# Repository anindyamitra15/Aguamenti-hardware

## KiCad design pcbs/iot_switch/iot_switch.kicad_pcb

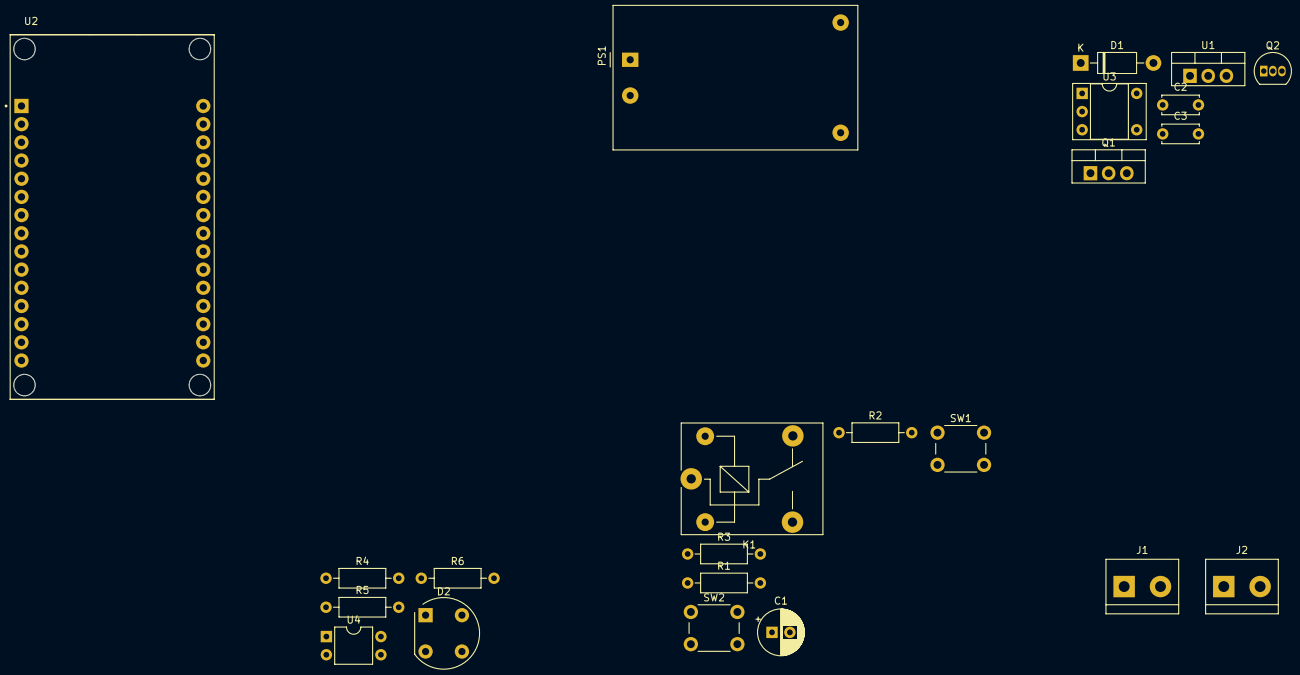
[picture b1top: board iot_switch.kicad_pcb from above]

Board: 2 copper layers, 23 parts (0 on the bottom side), 22 nets, no tracks yet.

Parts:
C1: 100uF; CP_Radial_D6.3mm_P2.50mm
C2, C3: 100nF; C_Disc_D5.0mm_W2.5mm_P5.00mm
D1: 1N4007; D_DO-41_SOD81_P10.16mm_Horizontal
D2: W10G; Diode_Bridge_Round_D9.8mm
J1: AC IN; TerminalBlock_bornier-2_P5.08mm
J2: LOAD OUT; TerminalBlock_bornier-2_P5.08mm
K1: SANYOU_SRD_Form_C; Relay_SPDT_SANYOU_SRD_Series_Form_C
PS1: HLK-PM12; Converter_ACDC_HiLink_HLK-PMxx
Q1: BT136-500; TO-220-3_Vertical
Q2: BC547; TO-92_Inline
R1, R3: 1k; R_Axial_DIN0207_L6.3mm_D2.5mm_P10.16mm_Horizontal
R2: 330; R_Axial_DIN0207_L6.3mm_D2.5mm_P10.16mm_Horizontal
R4, R5: 100k; R_Axial_DIN0207_L6.3mm_D2.5mm_P10.16mm_Horizontal
R6: 10k; R_Axial_DIN0207_L6.3mm_D2.5mm_P10.16mm_Horizontal
SW1: L1 Switch; SW_PUSH_6mm
SW2: L2 Switch; SW_PUSH_6mm
U1: L7805; TO-220-3_Vertical
U2: ESP32-DEVKIT-V1; MODULE_ESP32_DEVKIT_V1
U3: MOC3021M; DIP-5-6_W7.62mm_Socket
U4: PC817; DIP-4_W7.62mm

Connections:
+3V3: R6.1, U2.1
+5V: C3.1, U1.3, U2.30
+12V: C1.1, C2.1, D1.1, K1.2, PS1.4, U1.1
GND: C1.2, C2.2, C3.2, PS1.3, Q2.3, SW1.2, SW2.2, U1.2, U2.2, U2.29, U3.2, U4.3
L1: R1.2, U2.14
L2: R3.2, U2.15
Live: J1.1, K1.1, PS1.1, Q1.2, R4.1, U3.6
unnamed: D1.2, K1.5, Q2.1
unnamed: D2.1, U4.1
unnamed: D2.2, R5.2
unnamed: D2.3, U4.2
unnamed: J2.1, Q1.1
unnamed: J2.2, K1.3
unnamed: Q1.3, R2.1
unnamed: Q2.2, R3.1
unnamed: R1.1, U3.1
unnamed: R2.2, U3.4
unnamed: R4.2, R5.1
unnamed: SW1.1, U2.24
unnamed: SW2.1, U2.25
Neutral: D2.4, J1.2, PS1.2
ZVD: R6.2, U2.9, U4.4

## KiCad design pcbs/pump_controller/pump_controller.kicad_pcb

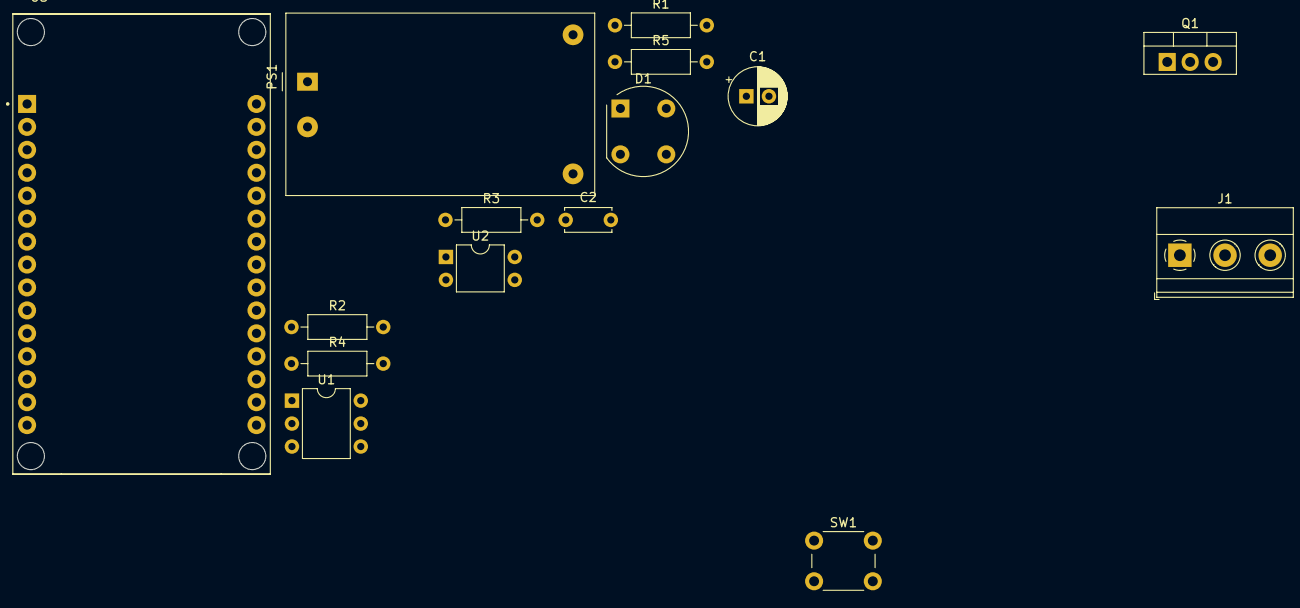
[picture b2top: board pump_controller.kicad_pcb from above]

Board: 2 copper layers, 15 parts (0 on the bottom side), 16 nets, no tracks yet.

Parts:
C1: 100uF; CP_Radial_D6.3mm_P2.50mm
C2: 100nF; C_Disc_D5.0mm_W2.5mm_P5.00mm
D1: W10G; Diode_Bridge_Round_D9.8mm
J1: AC_CON; TerminalBlock_Phoenix_MKDS-1,5-3_1x03_P5.00mm_Horizontal
PS1: HLK-PM01; Converter_ACDC_HiLink_HLK-PMxx
Q1: BTA16-800BW; TO-220-3_Vertical
R1, R2: 100k; R_Axial_DIN0207_L6.3mm_D2.5mm_P10.16mm_Horizontal
R3: 470; R_Axial_DIN0207_L6.3mm_D2.5mm_P10.16mm_Horizontal
R4: 1k; R_Axial_DIN0207_L6.3mm_D2.5mm_P10.16mm_Horizontal
R5: 10k; R_Axial_DIN0207_L6.3mm_D2.5mm_P10.16mm_Horizontal
SW1: Control Switch; SW_PUSH_6mm
U1: MOC3021M; DIP-6_W7.62mm
U2: PC817; DIP-4_W7.62mm
U3: ESP32-DEVKIT-V1; MODULE_ESP32_DEVKIT_V1

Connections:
+3V3: R5.1, U3.1
+5V: C1.1, C2.1, PS1.4, U3.30
Drive: R4.2, U3.6
GND: C1.2, C2.2, PS1.3, SW1.2, U1.2, U2.3, U3.2, U3.29
unnamed: D1.1, U2.1
unnamed: D1.2, R2.2
unnamed: D1.3, U2.2
unnamed: D1.4, J1.2, PS1.1, Q1.2, U1.4
unnamed: J1.1, Q1.1
unnamed: J1.3, PS1.2, R1.1
unnamed: Q1.3, R3.1
unnamed: R1.2, R2.1
unnamed: R3.2, U1.6
unnamed: R4.1, U1.1
unnamed: SW1.1, U3.7
ZVD: R5.2, U2.4, U3.9

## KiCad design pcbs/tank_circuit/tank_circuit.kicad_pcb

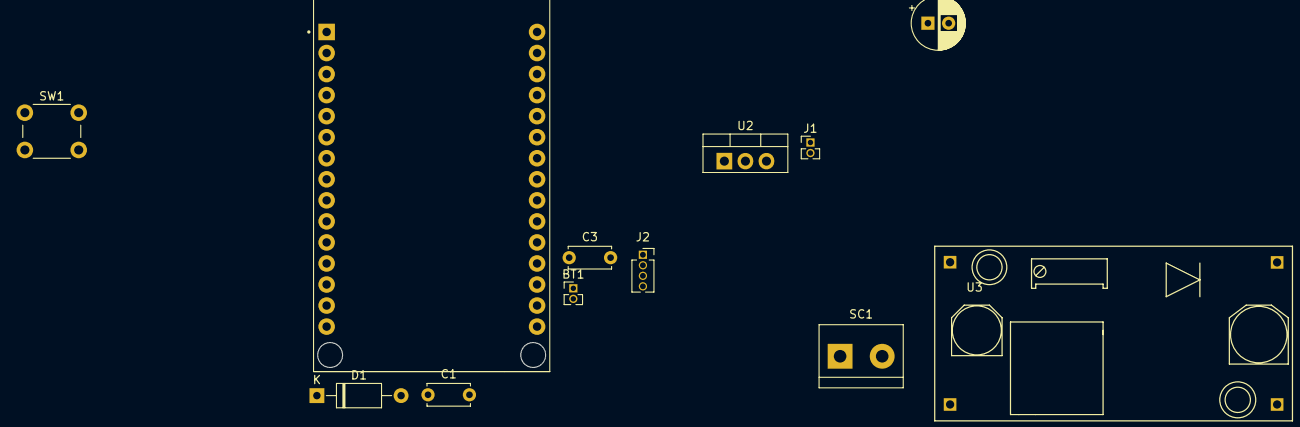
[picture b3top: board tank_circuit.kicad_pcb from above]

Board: 2 copper layers, 12 parts (0 on the bottom side), 10 nets, no tracks yet.

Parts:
BT1: 7.4V Li-ion; PinHeader_1x02_P1.27mm_Vertical
C1, C3: 100nF; C_Disc_D5.0mm_W2.5mm_P5.00mm
C2: 100uF; CP_Radial_D6.3mm_P2.50mm
D1: D_Schottky; D_A-405_P10.16mm_Horizontal
J1: Overflow detect; PinHeader_1x02_P1.27mm_Vertical
J2: Ultrasonic sensor; PinSocket_1x04_P1.27mm_Vertical
SC1: Solar_Cells; TerminalBlock_bornier-2_P5.08mm
SW1: Calibration mode; SW_PUSH_6mm
U1: ESP32-DEVKIT-V1; MODULE_ESP32_DEVKIT_V1
U2: LM7805_TO220; TO-220-3_Vertical
U3: XL6009; XL6009_module

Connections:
+5V: C1.1, J2.1, U1.30, U2.3
+VDC: BT1.1, C2.1, C3.1, D1.1, U2.1
GND: BT1.2, C1.2, C2.2, C3.2, J1.2, J2.4, SW1.2, U1.2, U1.29, U2.2, U3.3
unnamed: D1.2, U3.4
unnamed: J1.1, U1.9
unnamed: J2.2, U1.6
unnamed: J2.3, U1.7
unnamed: SC1.1, U3.1
unnamed: SC1.2, U3.2
unnamed: SW1.1, U1.10

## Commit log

2022-10-16 init
2022-10-16 some info
2022-10-16 added some library skeleton
2022-10-16 added VS code workspace to open all the firmware together from the parent file
2022-11-05 experiment program added
2022-11-05 new ping wokring
2022-11-06 http login working, socket needs to be fixed
2022-11-06 socket io connection working
2022-11-07 some improvisations on socket
2022-11-11 added schematic for generic board
2022-11-13 updated AP name and http connection failure code
2022-11-13 guru meditation error fixed
2022-11-13 endpoint subscription feature added
2022-11-13 moved endpoint to token
2022-11-14 removed unused function definition
2022-11-14 pump firmware at working stage
2022-11-15 tank firmware fully functional
2022-11-15 tomorrow's presentation ready
2022-11-15 today's presentation ready
2022-11-16 added tank pcb
2022-11-22 schematics updated
2022-11-22 iot switch zv detection section added
2022-11-23 added on/off switch to tank circuit
2022-11-24 endpoint signature modified
2022-11-24 generalised
2022-11-24 compacted the code
2022-11-24 new firmware for 2 channel board, added
2022-11-24 compacted
2022-11-25 changes according to switch prototype
2022-11-26 changes according to prototype
2022-11-26 fully working stage 1
2022-11-26 working on heroku
2022-11-27 working for heroku server
2023-05-21 changed to capacitor based water sensor by Arnab
2023-05-21 updated NetHandlers to use local network
